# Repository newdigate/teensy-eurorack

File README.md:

# teensy eurorack audio shield 

[![built with kicad](https://img.shields.io/badge/project-v5.1.6-brightgreen.svg?label=kicad&colorA=555555&colorB=8a8fff&logo=
)](https://kicad.org/)

Sponsored by:

**open source [hardware](hardware) and [software](https://github.com/newdigate/teensy-eurorack-software) for a 30-channel (14 in / 16 out) 16-bit analog [teensy 4.1](https://www.pjrc.com/store/teensy40.html "teensy 4.1 board") eurorack shield** 

* add peripherals to extend your [teensy 4.1](https://www.pjrc.com/store/teensy40.html "teensy 4.1 board") to interface with 
  * analog line audio (6 in / 8 out)
  * analog control voltages (8 in / 8 out: -10 to +10 volts)
  * midi in/out
  * microSD socket breakout
  * USB-A host and USB-B devices
  * 4 potentiometers, 3 encoders w/switch
* online designer [teensy eurorack audio gui](https://newdigate.github.io/teensy-eurorack-audio-gui) [^](https://github.com/newdigate/teensy-eurorack-audio-gui)

# updates 
  * 14 August 2021 : software and examples have moved to this repo [newdigate/teensy-eurorack-software](https://github.com/newdigate/teensy-eurorack-software)

# contents
* [sponsor](#sponsor)
* [specifications](#specifications)
* [license](#license)
* [open source software-stack](#open-source-software-stack)
* [build](#build)
  * [order pcbs](#order-pcbs)
  * [sourcing parts](#sourcing-parts)
    * [mouser boms](#mouser-boms)
    * [parts not on mouser boms](#parts-not-on-mouser-boms)
  * [interactive html boms online](#interactive-html-boms-online)
* [source code](#source-code)
* [improvements](#improvements)
* [printed circuit boards](#printed-circuit-boards)
  * [mainboard](#mainboard)
  * [breakout board](#breakout-board)
* [schematics](#schematics)  
* [panel design](#panel-design)  
* [assembly technical drawings](#assembly-technical-drawings)
* [youtube videos](#youtube-videos)
* [versions](#versions)
* [todo](#todo)
* [continuous-integration](#continuous-integration)
* [credits](#credits)
* [sponsored by](#sponsored-by)

# sponsor
* [patreon/teensy_eurorack](https://www.patreon.com/teensy_eurorack)
* paypal.me: [paypal.me/nicnewdigate](https://paypal.me/nicnewdigate)

# specifications
* **microcontrollers:** 
  * 600 Mhz ARM cortex m7 ( [teensy 4.1 board](https://www.pjrc.com/store/teensy41.html "teensy 4.1 board") )
* **audio:** multi-channel audio codec ( 6-in / 8-out 24-bit sound card - [CS42448](https://statics.cirrus.com/pubs/proDatasheet/CS42448_F5.pdf) )
  * *the audio codec circuit originally started as a discussion on quad audio channel outputs and a pcb design integrating teensy and cs42448 from Paul Stoffregen on [pjrc forum](https://forum.pjrc.com/threads/41371-Quad-channel-output-on-Teensy-3-6?p=138828&viewfull=1#post138828)*
* **analog control voltage ins/outs:** -10V to 10V 16bit/sample, 8 x inputs and 8 x outputs ( [ad7606](https://www.analog.com/media/en/technical-documentation/data-sheets/ad7606_7606-6_7606-4.pdf), 2x [ad5754](https://www.analog.com/media/en/technical-documentation/data-sheets/AD5724_5734_5754.pdf) )
* **display:** ST7735 128x128 16bit-color tft display
* **breakouts:** 
  * microSD card socket, 
  * USB host/device, 
  * midi in/out, 
  * knobs (4 x pots, 3 x encoders w/switch)
* **panel:** 24HP aluminium panel mounted for eurorack case
* **programability**: 
  * write arduino compatible c/c++ firmware & program using arduino/teensyduino
  * arm gnu toolchain [downloads](https://developer.arm.com/tools-and-software/open-source-software/developer-tools/gnu-toolchain/gnu-rm/downloads)
  * teensy [audio library](https://www.pjrc.com/teensy/gui/)

# license
* All artifacts are MIT license unless otherwise specified on a per file basis.

# open source software stack
* All [schematics](hardware/CIRCUITS.md) and boards are created using [Kicad](https://kicad.org/) 
* All mechanical designs are created using [FreeCAD](https://github.com/FreeCAD/FreeCAD)
* Some images have been rendered using [Blender 2.81](https://www.blender.org/)

# build
## order pcbs
* Use these gerber files to order 3 pcboards
  * the uSD-card extender should be about 0.6mm - 0.8mm thick
  * if you're using solder paste, you'll need to order the stencils of the bottom-side of main- and breakout boards.   
  
* [gerbers-breakout.zip](https://github.com/newdigate/teensy-eurorack/raw/master/hardware/gerbers/gerbers-breakout.zip)
* [gerbers-mainboard.zip](https://github.com/newdigate/teensy-eurorack/raw/master/hardware/gerbers/gerbers-mainboard.zip)
* [gerbers-uSD_extender_male.zip](https://github.com/newdigate/teensy-eurorack/raw/master/hardware/gerbers/gerbers-uSD_extender_male.zip)

## sourcing parts
Most parts are available from mouser.com - you can use the mouser BOMs below as a template to create an order. 

### mouser boms
* [mainboard](https://eu.mouser.com/ProjectManager/ProjectDetail.aspx?AccessID=e554cc1725)
* [breakoutboard](https://www.mouser.com/ProjectManager/ProjectDetail.aspx?AccessID=76e89a9e69)
### parts not on mouser boms
* panel: 
  * order from Front Panel Express: [.fpd](https://github.com/newdigate/teensy-eurorack/tree/master/hardware/panel/fpd)
    * for US: download [Front Panel Express](https://www.frontpanelexpress.com)
    * for Europe: download [Front Panel Designer](https://www.schaeffer-ag.de/en/front-panel-designer)
  * CNC your own with [FreeCad](https://www.freecadweb.org/downloads.php): [panel.FCStd](https://github.com/newdigate/teensy-eurorack/blob/master/hardware/panel/panel.FCStd) 
* mainboard:
  * 2.54mm pitch pin headers and sockets
    * J28: Eurorack power header: either male or female (2 x 8), I use female as my eurorack power (tip top) has male connectors. 
* breakout:
  * uSD card socket: [pjs008u-3000-0 yamaichi](https://octopart.com/pjs008u-3000-0-yamaichi-20649952?r=sp)
  * display: ST7735 (1.44 inch TFT LCD ST7735 SPI display module 128*128 8pin 65K color)

  * 16 x thonkiconns: [PJ398SM](https://www.thonk.co.uk/shop/thonkiconn)
  * 4 x 9mm snap-in pots: [alpha-9mm-pots](https://www.thonk.co.uk/shop/alpha-9mm-pots/) - You want linear (B-series) not audio (A-series) B5K or B10K should be ideal.
  * 3 x rotary encoders w/switches: Half axis (D-shaft) rotary encoder, handle/axis length: 20mm, EC11/EC12 digital potentiometer with switch - 5Pin

**Update**: USB-A-S-X-X-VT is no longer available. [Amphenol Commercial Products GSB11111ALF](https://mou.sr/3OmC2OO) looks like it may be a good replacement.

## interactive html boms online
  * [mainboard](https://newdigate.github.io/teensy-eurorack/teensy-eurorack)
  * [breakoutboard](https://newdigate.github.io/teensy-eurorack/teensy-eurorack-breakout)

# source code
 * Teensy Audio library drivers for ad5754, ad7606 via SPI
   * [teensy-audio-ad5754-ad7606](https://github.com/newdigate/teensy-audio-ad5754-ad7606)
 * simple standard midi file reader 
   * [midi-smf-reader](https://github.com/newdigate/midi-smf-reader)
 * generic sequencer
   * [teensy-quencer](https://github.com/newdigate/teensy-quencer)
 * variable rate playback
   * [teensy-variable-playback](https://github.com/newdigate/teensy-variable-playback)
 * oscilliscope and x/y scope display components
   * [teensy-audio-libtftscope](https://github.com/newdigate/teensy-audio-libtftscope)
 * cmake macros for compiling c++ for arm cortex 
   * [teensy-cmake-macros](https://github.com/newdigate/teensy-cmake-macros)
 * Audio level and CV level meters 
   * [teensy-audio-display-components](https://github.com/newdigate/teensy-audio-display-components)

# improvements
At this point Im just focusing on finalising/polishing the current version, but there are some improvements I'd like to make at some point.
* add 4x jack sockets for analog output of knobs on breakout board. 
* use 3.5mm jack sockets (as well as standard midi din connectors) for midi in and out. 
* switch to active audio input and output circuitry, allow switchable 0dB / 12dB gain, for guitar signals.
* let me know if you're think there something else that can be improved, added, removed. 

There is a journal of my progress (its a bit out of date, sorry) - [journal.md](hardware/JOURNAL.md) 

**What you can do if you like to see progress with this project?**
* [#sponsor](#sponsor)...
* star this repository (means you need a github account - go for it!!)
* subscribe [Nic N on youtube](https://www.youtube.com/channel/UChMicDp8wUXYzBhEN-Wvb5g) 
* download kicad and freecad, clone this repo, make improvements, commit & send pull-requests, and raise issues...

# printed circuit boards
## [mainboard](hardware/boards/mainboard) 
* standard double layer printed circuit board
  * thinkness: 1.6mm  
  * minimum trace: 6 mil
  * minimum clearance: 6 mil
  * dimension: 118mm*102mm
* socket to connect teensy 4.0 board
* cs42448 audio codec 
* 3 x stereo 6.35mm TRS jack inputs
* 4 x stereo 6.35mm TRS jack outputs
* pin sockets to connect breakout board

## breakout board
* 2 layer printed circuit board
  * thinkness: 1.6mm  
  * minimum trace: 6 mil
  * minimum clearance: 6 mil
  * dimension: 110mm*111mm
* 8 x 3.5mm jack socket for analog control voltage inputs
* 8 x 3.5mm jack socket for analog control voltage outputs
* midi in/out DIN sockets
* usb device/host
  * USB-B: USB device mode
  * USB-A: USB host mode
* micro-SD card socket
* 4 x linear pots
* 3 x rotary encoders with switches 

# schematics

# [panel design](hardware/panel)

# assembly technical drawings 

# youtube videos 
* [Nic N](https://www.youtube.com/channel/UChMicDp8wUXYzBhEN-Wvb5g) 
  * [youtube: Assembling custom eurorack audio shield for teensy 4.1](https://www.youtube.com/watch?v=PzaJ3Wq1Fsc)
  * [youtube: Teensy 4.0 eurorack shield design intro](https://www.youtube.com/watch?v=aNUSEszbnYU)
  * [youtube: 0v to 10v control voltage input, output and display using teensy 4.0](https://www.youtube.com/watch?v=5d5x8F7HRko)
  * [youtube: DIY assembly build - teensy 4.0 eurorack audio module](https://www.youtube.com/watch?v=oZzPgpTrEhc)
  * [youtube: assembly teensy eurorack shield](https://www.youtube.com/watch?v=Jx2KgpoT3WY)
  * [youtube: assembly timelapse](https://www.youtube.com/watch?v=s-514rDjirY)
  * [youtube: Eurorack digital audio modules powered by teensy micro-controller](https://www.youtube.com/watch?v=6zt6OF7UOTc)
  * [youtube: side-channel stereo audio separation with teensy 4.0](https://www.youtube.com/watch?v=N0IBevm4hTQ)

# versions
## v2.1 (Saturday 3 April 2021)
* **Improvement**: Mainboard: Tie LRCLK pin 20 to pin40 to sync DAC/ADC sampling w/ audio sampling
* **FIXED**: breakout: add 1k pull-up resistor to MIDI rx pin
* mainboard: silkscreen: add Kicad OpenSourceHardware logo
* breakout: silkscreen: add Kicad OpenSourceHardware logo

## v2.0.3 (Saturday 13/02/2021)
* breakout: st7735 display changed vcc, reset, backlight from 5v to 3v3.

## v2.0.2 (31/01/2021)
* Mainboard: spaced out traces as there appeared to be some interference under certain circumstances.

## v2.0.1 (27/01/2021) 
* Mainboard: add daisy chain TX/RX connector on back side to communicate between multiple boards
* Breakout board: changed back to double layer board.

## v2.0.0(b)
* Breakout board: Corrected polarity of +-12V pin headers on breakout board (ouch!!!)
* change ADC to use external 2.5v voltage reference, same as DAC voltage reference now 

## v2.0.0
* SPI: separated ADC, DAC from display: 
  * st7735 display has its own dedicated SPI - (SPI0, stays the same)
  * ADC / DAC are now sharing SPI1
* integrated ADC and DAC into teensy audio library.
* added one more ad5754 DAC for total of 8 control voltage analog output channels

## v1.9.1b
* mainboard: correction: reconnected LRCLK to codec.

## v1.9.1
* connected DAC_SCK output (pin 19) to pin 31
  * allow cable select to be asserted on minor spi data cycle after every 24 or 48 spi clock cycles, using interrupt on pin 31.
    * hopefully this will allow DMA spi transfers to AD5754 and which will make integration with teensy audio library much easier

## v1.9 
updated to teesy 4.1 and improvements to make easier to build
* updated from teensy 4.0 to teensy 4.1
* schematic, footprint and pcb clean-up 
  * replaced footprints imported from eagle with native kicad footprints
* removed atmel samd21 and gpio ICs
* replaced gpio with AD5754 (extra 4 DAC channels)
* replaced RGB encoders with regular encoders
* replaced analog-GND-to-digital-GND footprint with a 0805 zero ohm resistor footprint. (DRC checks can pass now...)
* (temporarily) removed serial TX/RX to unused eurorack power pins
  
# todo 
- [x] ~~finalize design / circuits / boards~~
- [x] ~~order~~ (v.2.1)
- [x] ~~assemble~~
- [x] ~~testing~~
  - [x] ~~CS42448 audio codec~~
    - [x] ~~Audio input~~
    - [x] ~~Audio output~~
  - [x] ~~control voltage input~~
  - [x] ~~control voltage output~~
  - [x] ~~usb host~~
  - [x] ~~usb device~~
  - [x] ~~midi in~~
  - [x] ~~midi out~~
  - [x] ~~st7735 display~~
  - [x] ~~sd card extension & adapter~~
- [ ] Document 
  - [ ] order & build process
  - [ ] software process
- [ ] Firmware

# continuous-integration 
* testing automated build and packaging 
* [github.com/pwuertz/kicad_picknplace_assistant](https://github.com/pwuertz/kicad_picknplace_assistant)
* [github.com/productize/kicad-automation-scripts](https://github.com/productize/kicad-automation-scripts)
* [InteractiveHtmlBom](https://github.com/openscopeproject/InteractiveHtmlBom) by [openscopeproject](https://github.com/openscopeproject)

# credits 
* https://github.com/dgouramanis/usdextendercable

# sponsored by
Massive thanks to these generous people who have provided support!
* Hannes Schnaitter
* Daniel Hengeveld [thedaniel on github](https://github.com/thedaniel)
* Derek Brost
* Martin Eigel
* Morgan Massens

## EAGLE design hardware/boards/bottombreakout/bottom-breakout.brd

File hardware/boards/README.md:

# boards
 * [mainboard](#mainboard)
 * [breakout](#breakout)
 
All circuit boards are standard double layer boards with minimum 6 mil clearance and 6 mil traces. 

I have been using jlcpcb to fabricate my circuit boards.  

## [mainboard](mainboard) 

[mainboard design files](mainboard)

### [breakout](knobs-controller) 

[breakout design files](knobs-controller)

# assembly technical drawings

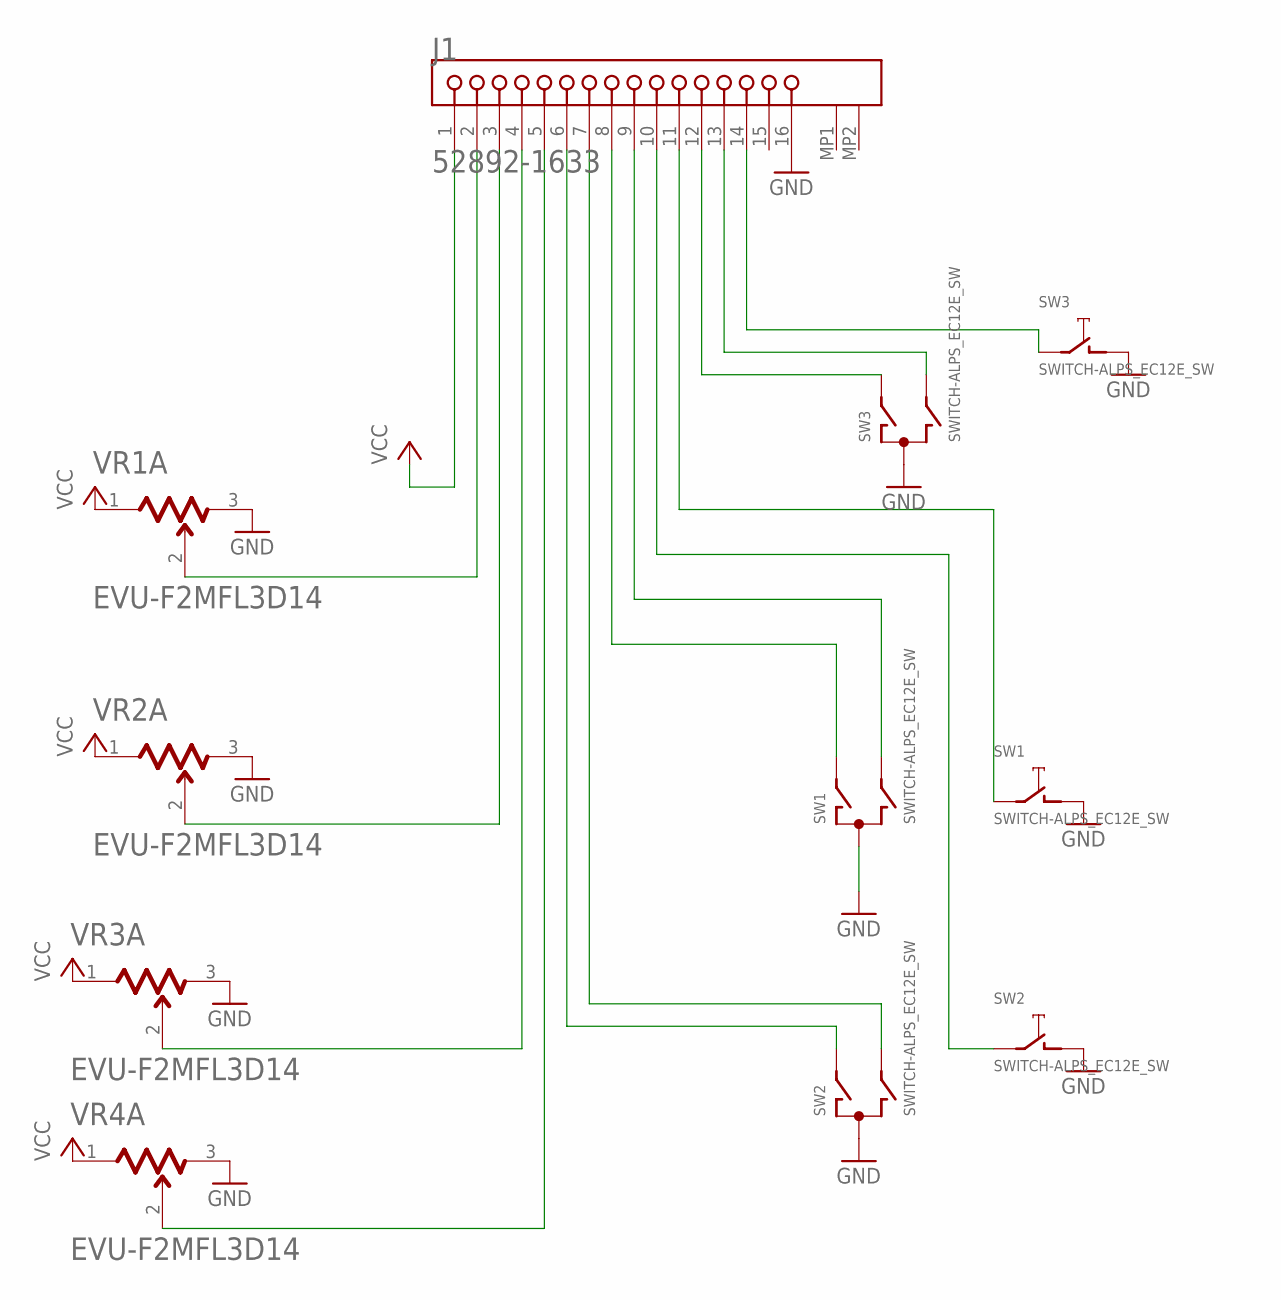
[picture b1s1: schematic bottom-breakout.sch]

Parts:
J1: MOLEX_52892-1633MOLEX_52892-1633_0_0; MOLEX_52892-1633_0
SW1, SW2, SW3: SWITCH-ALPS_EC12E_SW; SWITCH-ALPS_ALPS_EC12E_SW
VR1, VR2, VR3, VR4: PANASONIC_EVU-F2MFL3D14PANASONIC_EVU-F2MFL3D14_0_0; PANASONIC_EVU-F2MFL3D14_0

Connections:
GND: J1.16, SW1.C, SW1.D (1), SW2.C, SW2.D (1), SW3.C, SW3.D (1), VR1.3, VR2.3, VR3.3, VR4.3
unnamed: J1.2, VR1.2
unnamed: J1.3, VR2.2
unnamed: J1.4, VR3.2
unnamed: J1.6, SW2.A
unnamed: J1.7, SW2.B
unnamed: J1.8, SW1.A
unnamed: J1.9, SW1.B
unnamed: J1.10, SW2.E (2)
unnamed: J1.11, SW1.E (2)
unnamed: J1.5, VR4.2
unnamed: J1.12, SW3.A
unnamed: J1.13, SW3.B
unnamed: J1.14, SW3.E (2)
VCC: J1.1, VR1.1, VR2.1, VR3.1, VR4.1

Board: 2 copper layers, 8 parts (1 on the bottom side), 15 nets, no tracks yet.

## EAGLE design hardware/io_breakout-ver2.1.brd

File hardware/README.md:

# schematics, printed circuit boards, and panels
* schematic and circuit board files for both boards [here](boards)
* panel designs [here](panel)

# circuits images

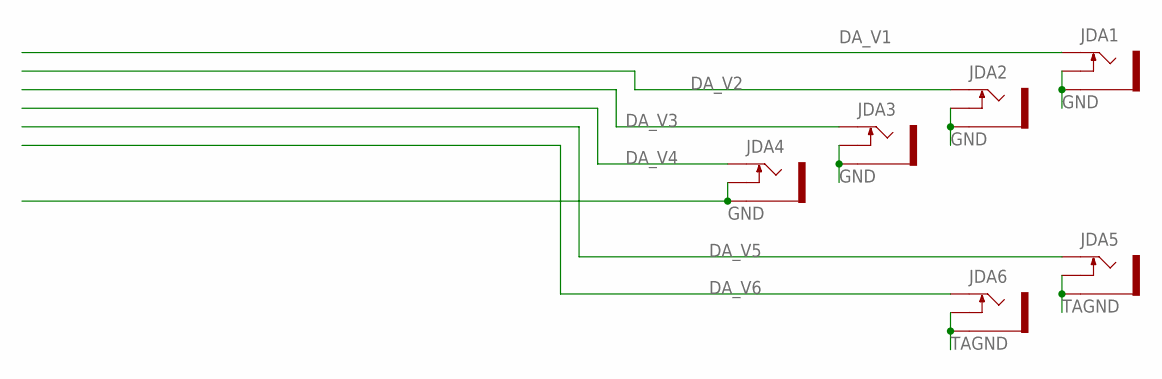
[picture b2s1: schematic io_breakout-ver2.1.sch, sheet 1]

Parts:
JDA1, JDA2, JDA3, JDA4, JDA5, JDA6: THONKICONNNEW; WQP-PJ301M-12_JACK

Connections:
DA_V1: JDA1.P$1_TIP (TIP); also elsewhere on the board
DA_V2: JDA2.P$1_TIP (TIP); also elsewhere on the board
DA_V3: JDA3.P$1_TIP (TIP); also elsewhere on the board
DA_V4: JDA4.P$1_TIP (TIP); also elsewhere on the board
DA_V5: JDA5.P$1_TIP (TIP); also elsewhere on the board
DA_V6: JDA6.P$1_TIP (TIP); also elsewhere on the board
GND: JDA1.P$2_SWITCH (SWITCH), JDA1.P$3_SLEEVE (SLEEVE), JDA2.P$2_SWITCH (SWITCH), JDA2.P$3_SLEEVE (SLEEVE), JDA3.P$2_SWITCH (SWITCH), JDA3.P$3_SLEEVE (SLEEVE), JDA4.P$2_SWITCH (SWITCH), JDA4.P$3_SLEEVE (SLEEVE); also elsewhere on the board
TAGND: JDA5.P$2_SWITCH (SWITCH), JDA5.P$3_SLEEVE (SLEEVE), JDA6.P$2_SWITCH (SWITCH), JDA6.P$3_SLEEVE (SLEEVE); also elsewhere on the board

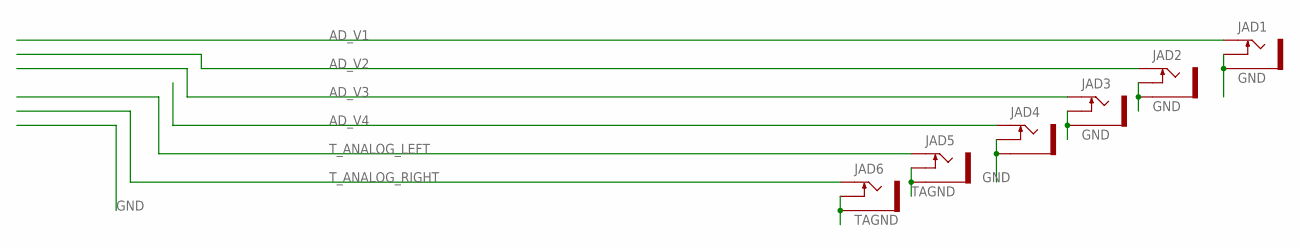
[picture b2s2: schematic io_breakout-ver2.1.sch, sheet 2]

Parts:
JAD1, JAD2, JAD3, JAD4, JAD5, JAD6: THONKICONNNEW; WQP-PJ301M-12_JACK

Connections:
AD_V1: JAD1.P$1_TIP (TIP); also elsewhere on the board
AD_V2: JAD2.P$1_TIP (TIP); also elsewhere on the board
AD_V3: JAD3.P$1_TIP (TIP); also elsewhere on the board
AD_V4: JAD4.P$1_TIP (TIP); also elsewhere on the board
GND: JAD1.P$2_SWITCH (SWITCH), JAD1.P$3_SLEEVE (SLEEVE), JAD2.P$2_SWITCH (SWITCH), JAD2.P$3_SLEEVE (SLEEVE), JAD3.P$2_SWITCH (SWITCH), JAD3.P$3_SLEEVE (SLEEVE), JAD4.P$2_SWITCH (SWITCH), JAD4.P$3_SLEEVE (SLEEVE); also elsewhere on the board
TAGND: JAD5.P$2_SWITCH (SWITCH), JAD5.P$3_SLEEVE (SLEEVE), JAD6.P$2_SWITCH (SWITCH), JAD6.P$3_SLEEVE (SLEEVE); also elsewhere on the board
T_ANALOG_LEFT: JAD5.P$1_TIP (TIP)
T_ANALOG_RIGHT: JAD6.P$1_TIP (TIP); also elsewhere on the board

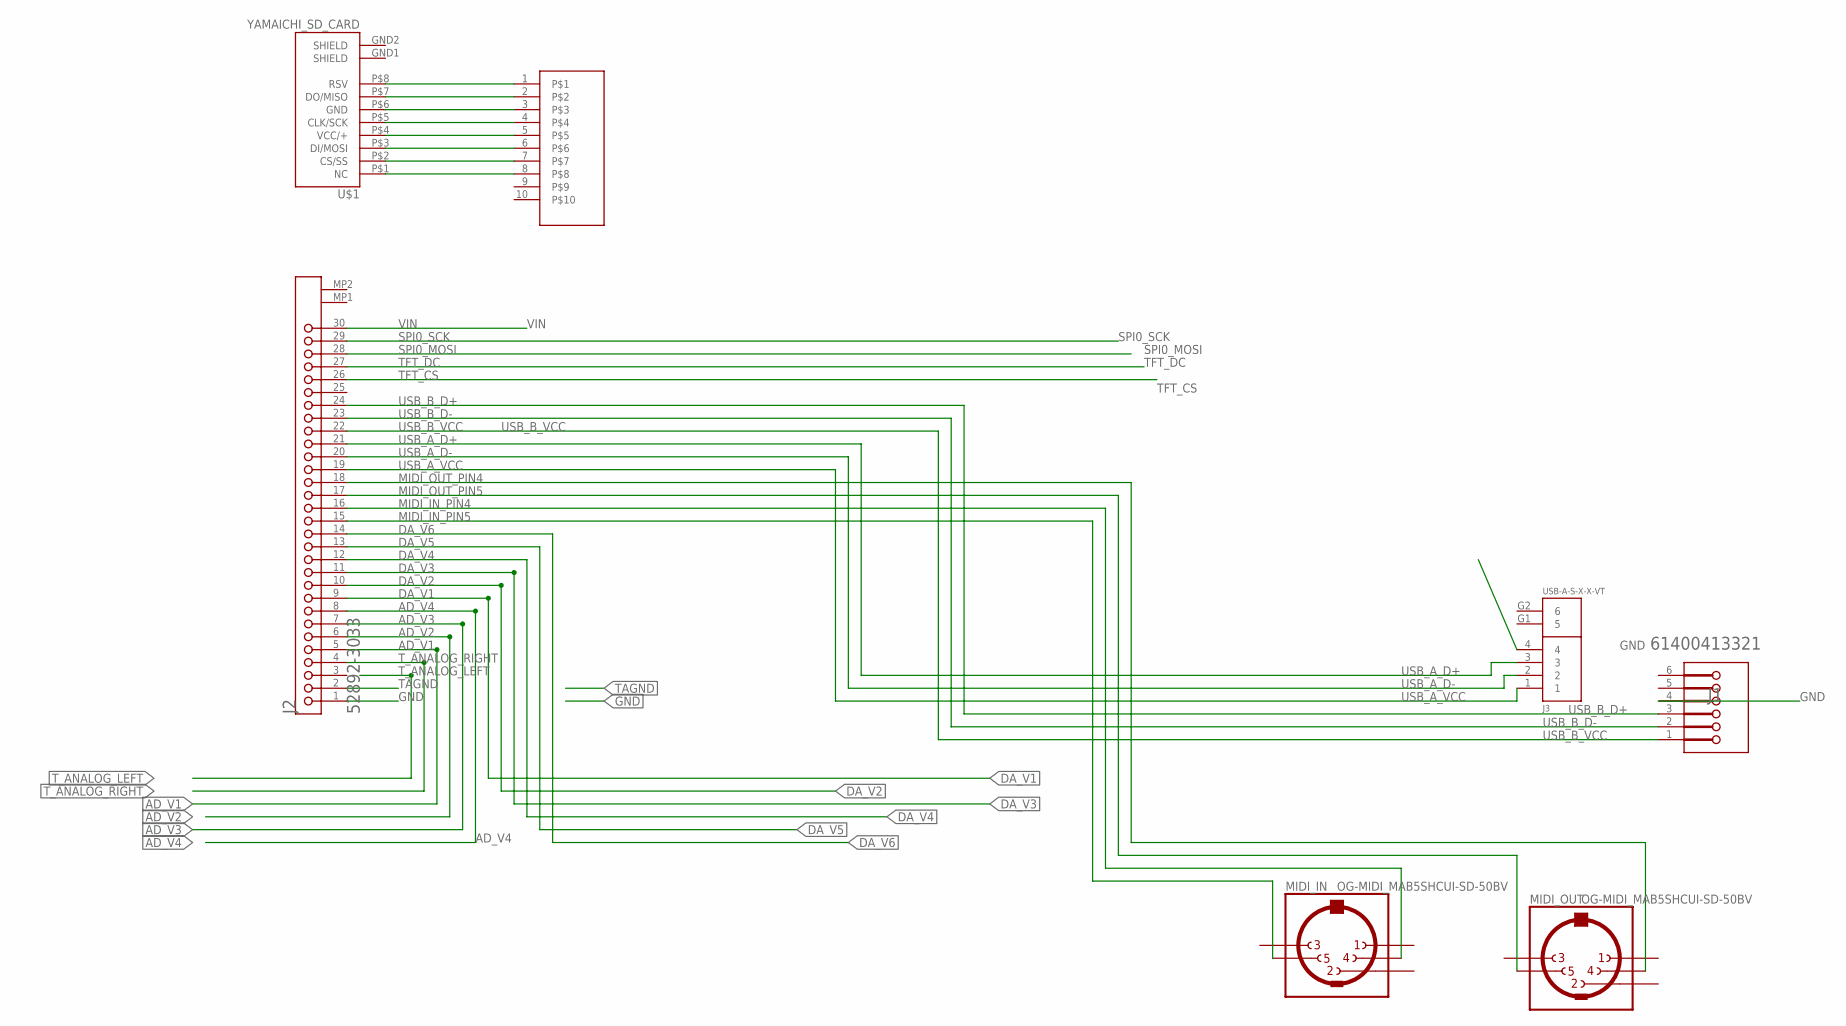
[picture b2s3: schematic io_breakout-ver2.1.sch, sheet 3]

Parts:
J1: WURTH_ELECTRONICS_61400413321WURTH_ELECTRONICS_61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; WURTH_ELECTRONICS_61400413321_0
J2: MOLEX_52892-3033MOLEX_52892-3033_0_0; MOLEX_52892-3033_0
J3: USB-A-S-X-X-VT
MIDI_IN: OG-MIDI_MAB5SHCUI-SD-50BV; OG-MIDI_SD-50BV
MIDI_OUT: OG-MIDI_MAB5SHCUI-SD-50BV; OG-MIDI_SD-50BV
U$1: YAMAICHI_SD_CARD; YAMAICHI_MICROSD_VERTICAL
U$2: 1734592-8; TE_1-1734592-8

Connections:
AD_V1: J2.5; also elsewhere on the board
AD_V2: J2.6; also elsewhere on the board
AD_V3: J2.7; also elsewhere on the board
AD_V4: J2.8; also elsewhere on the board
DA_V1: J2.9; also elsewhere on the board
DA_V2: J2.10; also elsewhere on the board
DA_V3: J2.11; also elsewhere on the board
DA_V4: J2.12; also elsewhere on the board
DA_V5: J2.13; also elsewhere on the board
DA_V6: J2.14; also elsewhere on the board
GND: J1.4, J2.1, J3.4; also elsewhere on the board
MIDI_IN_PIN4: J2.16, MIDI_IN.4
MIDI_IN_PIN5: J2.15, MIDI_IN.5
MIDI_OUT_PIN4: J2.18, MIDI_OUT.4
MIDI_OUT_PIN5: J2.17, MIDI_OUT.5
unnamed: U$1.P$8 (RSV), U$2.1
unnamed: U$1.P$7 (DO/MISO), U$2.2
unnamed: U$1.P$6 (GND), U$2.3
unnamed: U$1.P$5 (CLK/SCK), U$2.4
unnamed: U$1.P$3 (DI/MOSI), U$2.6
unnamed: U$1.P$4 (VCC/+), U$2.5
unnamed: U$1.P$2 (CS/SS), U$2.7
unnamed: U$1.P$1 (NC), U$2.8
SPI0_MOSI: J2.28; also elsewhere on the board
SPI0_SCK: J2.29; also elsewhere on the board
TAGND: J2.2; also elsewhere on the board
TFT_CS: J2.26; also elsewhere on the board
TFT_DC: J2.27; also elsewhere on the board
T_ANALOG_RIGHT: J2.4; also elsewhere on the board
USB_A_D+: J2.21, J3.3
USB_A_D-: J2.20, J3.2
USB_A_VCC: J2.19, J3.1
USB_B_D+: J1.3, J2.24
USB_B_D-: J1.2, J2.23
USB_B_VCC: J1.1, J2.22
VIN: J2.30; also elsewhere on the board

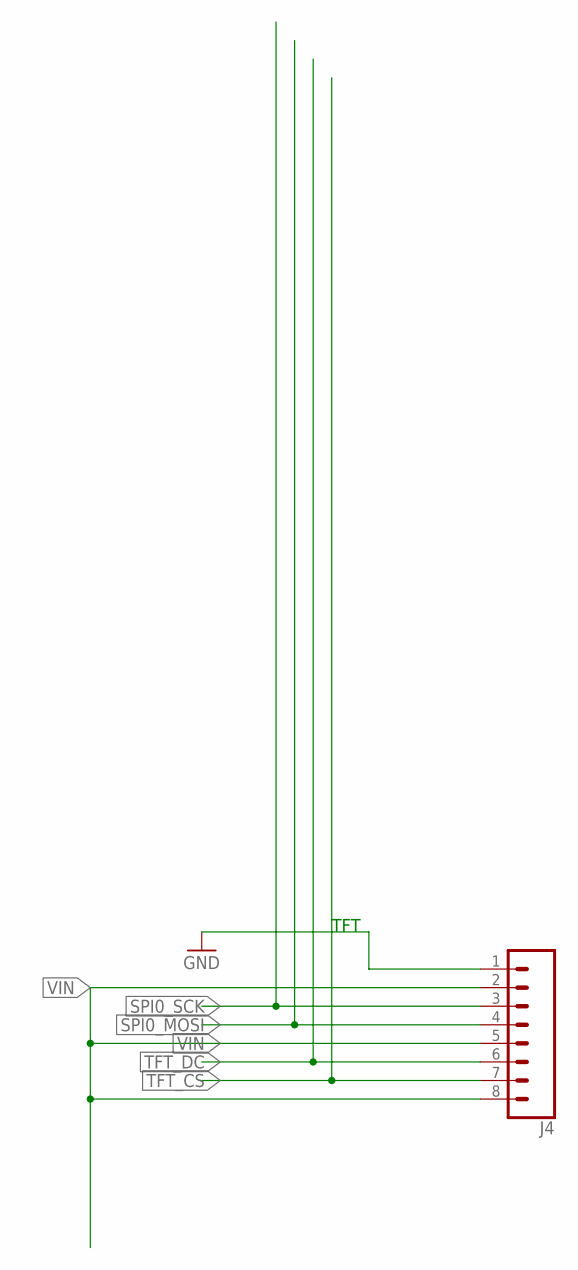
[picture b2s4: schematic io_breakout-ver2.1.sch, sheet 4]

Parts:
J4: ST7735_1.4; ST7735

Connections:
GND: J4.1 (GND); also elsewhere on the board
SPI0_MOSI: J4.4 (SDA); also elsewhere on the board
SPI0_SCK: J4.3 (SCL); also elsewhere on the board
TFT_CS: J4.7 (CS); also elsewhere on the board
TFT_DC: J4.6 (DC); also elsewhere on the board
VIN: J4.2 (VCC), J4.5 (RESET), J4.8 (BACKLIGHT); also elsewhere on the board

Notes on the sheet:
TFT

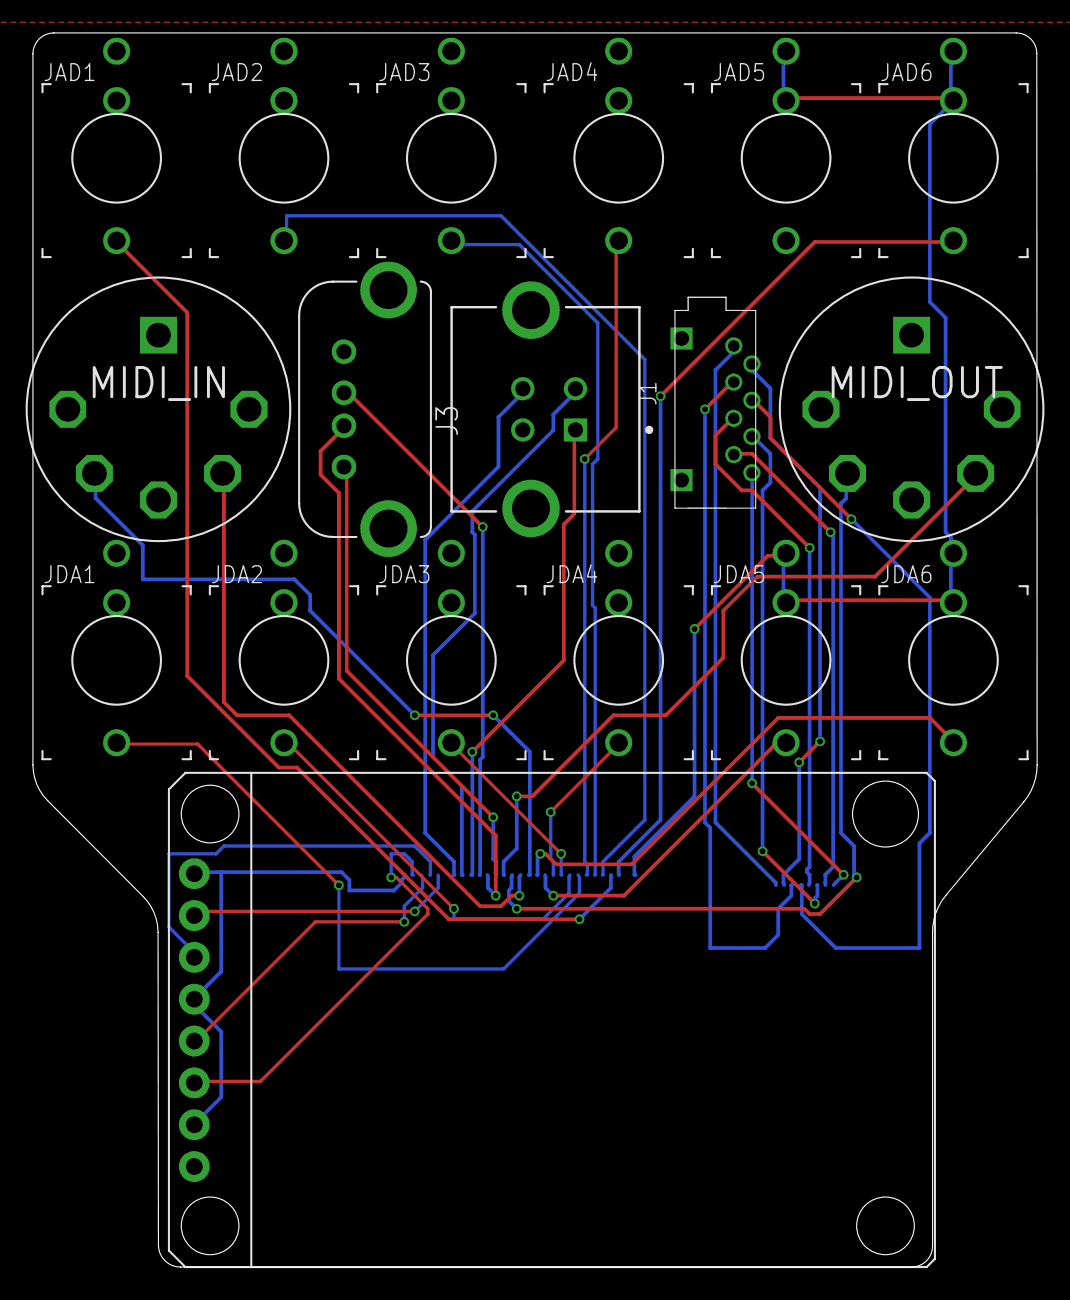
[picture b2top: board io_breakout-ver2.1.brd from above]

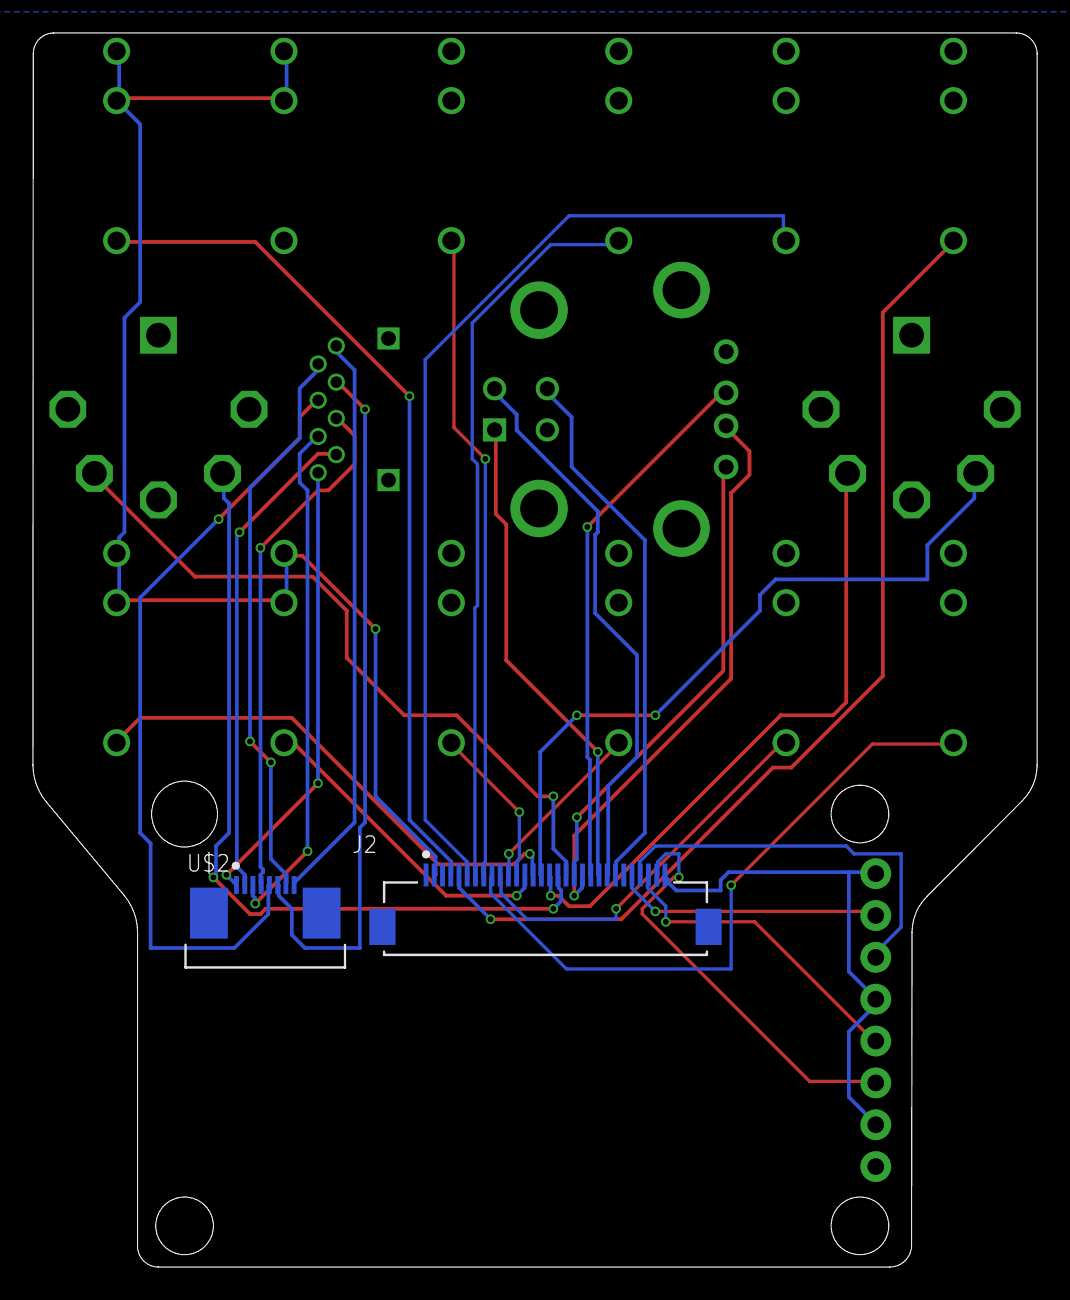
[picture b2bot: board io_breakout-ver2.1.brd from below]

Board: 2 copper layers, 61.0 x 74.9 mm, 20 parts (2 on the bottom side), 36 nets.

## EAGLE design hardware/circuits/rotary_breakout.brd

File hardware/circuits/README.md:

# circuits
* mainboard 

* jacks and midi - front panel pcb
	
* rotarty encoders - front panel pcb 

* sd card extender - front panel pcb)

* teensy to mainboard breakout pcb

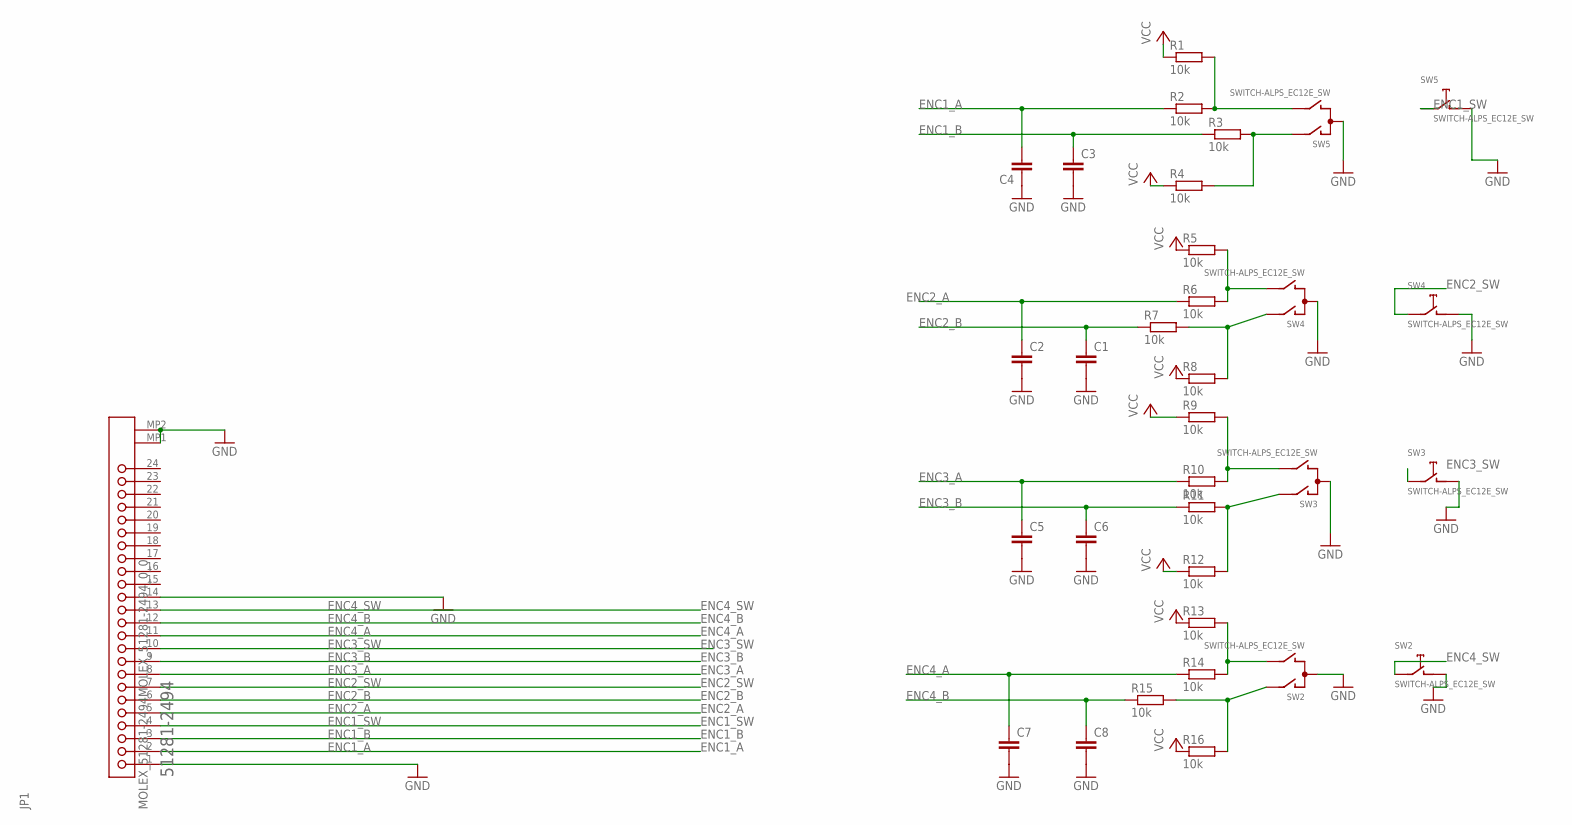
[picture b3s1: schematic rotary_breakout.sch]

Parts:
C1, C2, C3, C4, C5, C6, C7, C8: C-EUC0805; C0805
JP1: MOLEX_51281-2494MOLEX_51281-2494_0_0; MOLEX_51281-2494_0
R1, R2, R3, R4, R5, R6, R7, R8, R9, R10, R11, R12, R13, R14, R15, R16: 10k; R0603
SW2, SW3, SW4, SW5: SWITCH-ALPS_EC12E_SW; SWITCH-ALPS_ALPS_EC12E_SW

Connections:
ENC1_A: C4.2, JP1.2, R2.1
ENC1_B: C3.1, JP1.3, R3.1
ENC1_SW: JP1.4, SW5.E (2)
ENC2_A: C2.1, JP1.5, R6.1
ENC2_B: C1.1, JP1.6, R7.1
ENC2_SW: JP1.7, SW4.E (2)
ENC3_A: C5.1, JP1.8, R10.1
ENC3_B: C6.1, JP1.9, R11.1
ENC3_SW: JP1.10, SW3.E (2)
ENC4_A: C7.1, JP1.11, R14.1
ENC4_B: C8.1, JP1.12, R15.1
ENC4_SW: JP1.13, SW2.E (2)
GND: C1.2, C2.2, C3.2, C4.1, C5.2, C6.2, C7.2, C8.2, JP1.1, JP1.14, JP1.MP1, JP1.MP2, SW2.C, SW2.D (1), SW3.C, SW3.D (1), SW4.C, SW4.D (1), SW5.C, SW5.D (1)
unnamed: R1.2, R2.2, SW5.B
unnamed: R5.2, R6.2, SW4.B
unnamed: R9.2, R10.2, SW3.B
unnamed: R13.2, R14.2, SW2.B
unnamed: R7.2, R8.2, SW4.A
unnamed: R11.2, R12.2, SW3.A
unnamed: R15.2, R16.2, SW2.A
unnamed: R3.2, R4.2, SW5.A
VCC: R1.1, R4.1, R5.1, R8.1, R9.1, R12.1, R13.1, R16.1

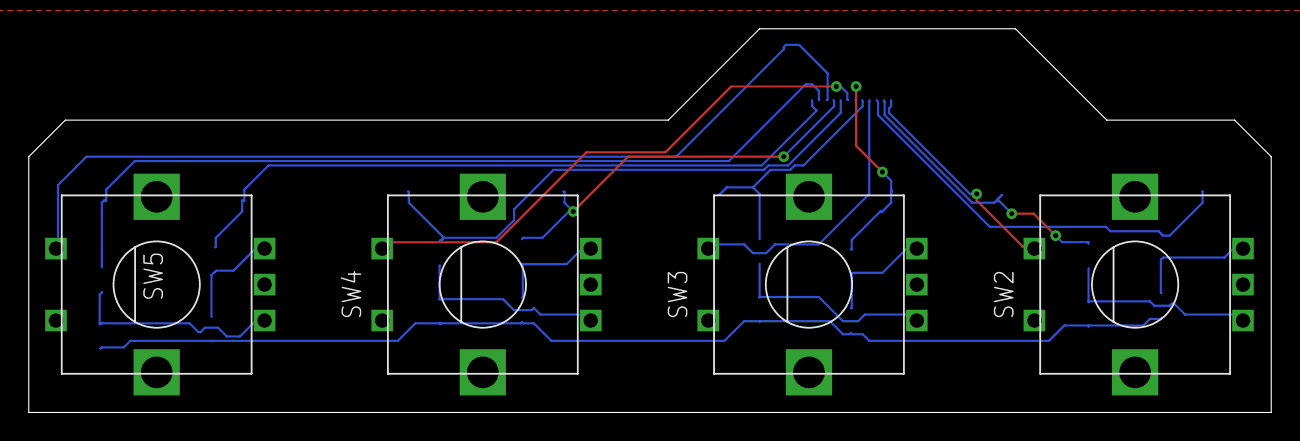
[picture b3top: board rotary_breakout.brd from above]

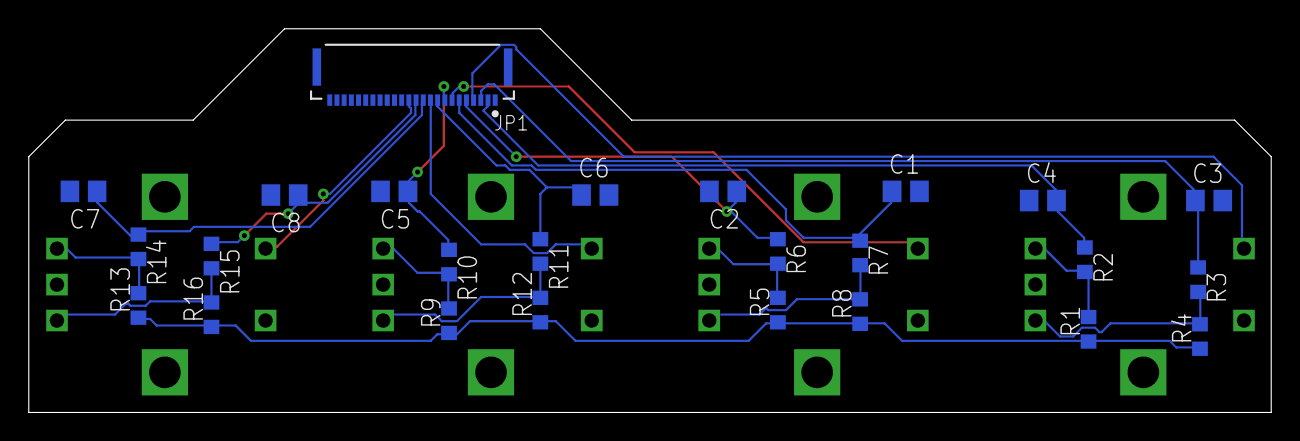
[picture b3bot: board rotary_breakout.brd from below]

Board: 2 copper layers, 86.4 x 26.7 mm, 29 parts (25 on the bottom side), 22 nets.

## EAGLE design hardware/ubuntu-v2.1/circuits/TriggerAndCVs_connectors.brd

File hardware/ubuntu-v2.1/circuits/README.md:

# circuits
* mainboard 

* jacks and midi - front panel pcb
	
* rotarty encoders - front panel pcb 

* sd card extender - front panel pcb)

* teensy to mainboard breakout pcb

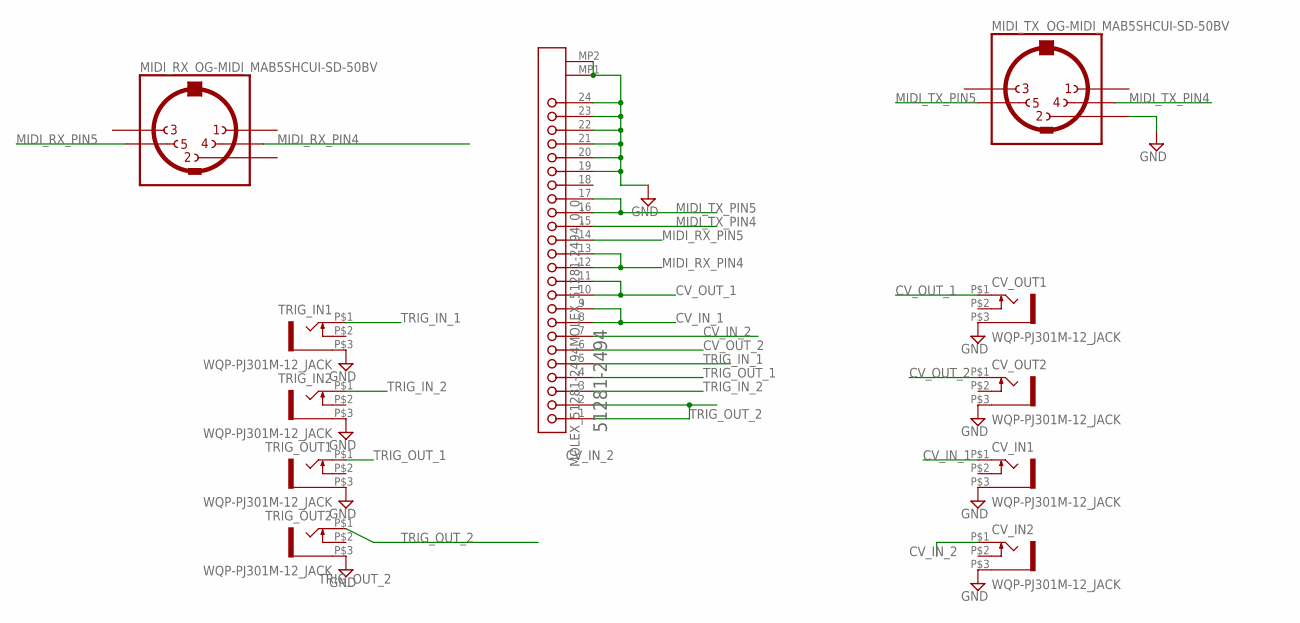
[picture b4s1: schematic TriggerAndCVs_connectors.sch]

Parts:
CV_IN1, CV_IN2: WQP-PJ301M-12_JACK
CV_OUT1, CV_OUT2: WQP-PJ301M-12_JACK
JP4: MOLEX_51281-2494MOLEX_51281-2494_0_0; MOLEX_51281-2494_0
MIDI_RX: OG-MIDI_MAB5SHCUI-SD-50BV; OG-MIDI_SD-50BV
MIDI_TX: OG-MIDI_MAB5SHCUI-SD-50BV; OG-MIDI_SD-50BV
TRIG_IN1, TRIG_IN2: WQP-PJ301M-12_JACK
TRIG_OUT1, TRIG_OUT2: WQP-PJ301M-12_JACK

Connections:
CV_IN_1: CV_IN1.P$1 (2), JP4.8, JP4.9
CV_IN_2: CV_IN2.P$1 (2), JP4.7
CV_OUT_1: CV_OUT1.P$1 (2), JP4.10, JP4.11
CV_OUT_2: CV_OUT2.P$1 (2), JP4.6
GND: CV_IN1.P$3 (1), CV_IN2.P$3 (1), CV_OUT1.P$3 (1), CV_OUT2.P$3 (1), JP4.19, JP4.20, JP4.21, JP4.22, JP4.23, JP4.24, JP4.MP1, JP4.MP2, MIDI_TX.2, TRIG_IN1.P$3 (1), TRIG_IN2.P$3 (1), TRIG_OUT1.P$3 (1), TRIG_OUT2.P$3 (1)
MIDI_RX_PIN4: JP4.12, JP4.13, MIDI_RX.4
MIDI_RX_PIN5: JP4.14, MIDI_RX.5
MIDI_TX_PIN4: JP4.15, MIDI_TX.4
MIDI_TX_PIN5: JP4.16, JP4.17, MIDI_TX.5
TRIG_IN_1: JP4.5, TRIG_IN1.P$1 (2)
TRIG_IN_2: JP4.3, TRIG_IN2.P$1 (2)
TRIG_OUT_1: JP4.4, TRIG_OUT1.P$1 (2)
TRIG_OUT_2: JP4.1, JP4.2, TRIG_OUT2.P$1 (2)

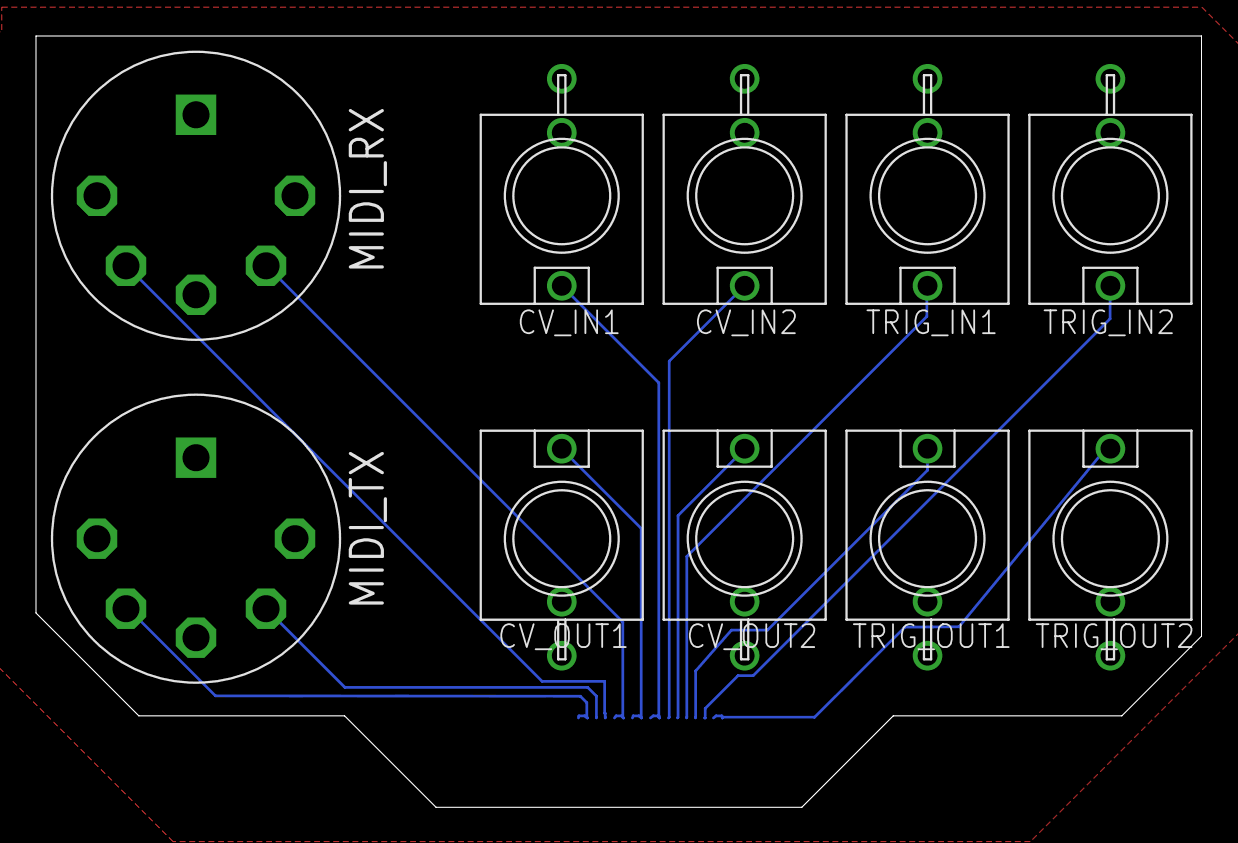
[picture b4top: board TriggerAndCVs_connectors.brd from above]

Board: 2 copper layers, 64.8 x 42.9 mm, 11 parts (1 on the bottom side), 13 nets.

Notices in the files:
parts and their libraries:
SparkFun-Switches: Licensing: Creative Commons ShareAlike 4.0 International - https://creativecommons.org/licenses/by-sa/4.0
cirrus: Copyright (C) 2008, Bob Starr
